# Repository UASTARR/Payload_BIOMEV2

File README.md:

# Payload_BIOMEV2

## TO-DO
- UART
  - ZE27-O3
- Power Distribution
- Connecting SPI and Power

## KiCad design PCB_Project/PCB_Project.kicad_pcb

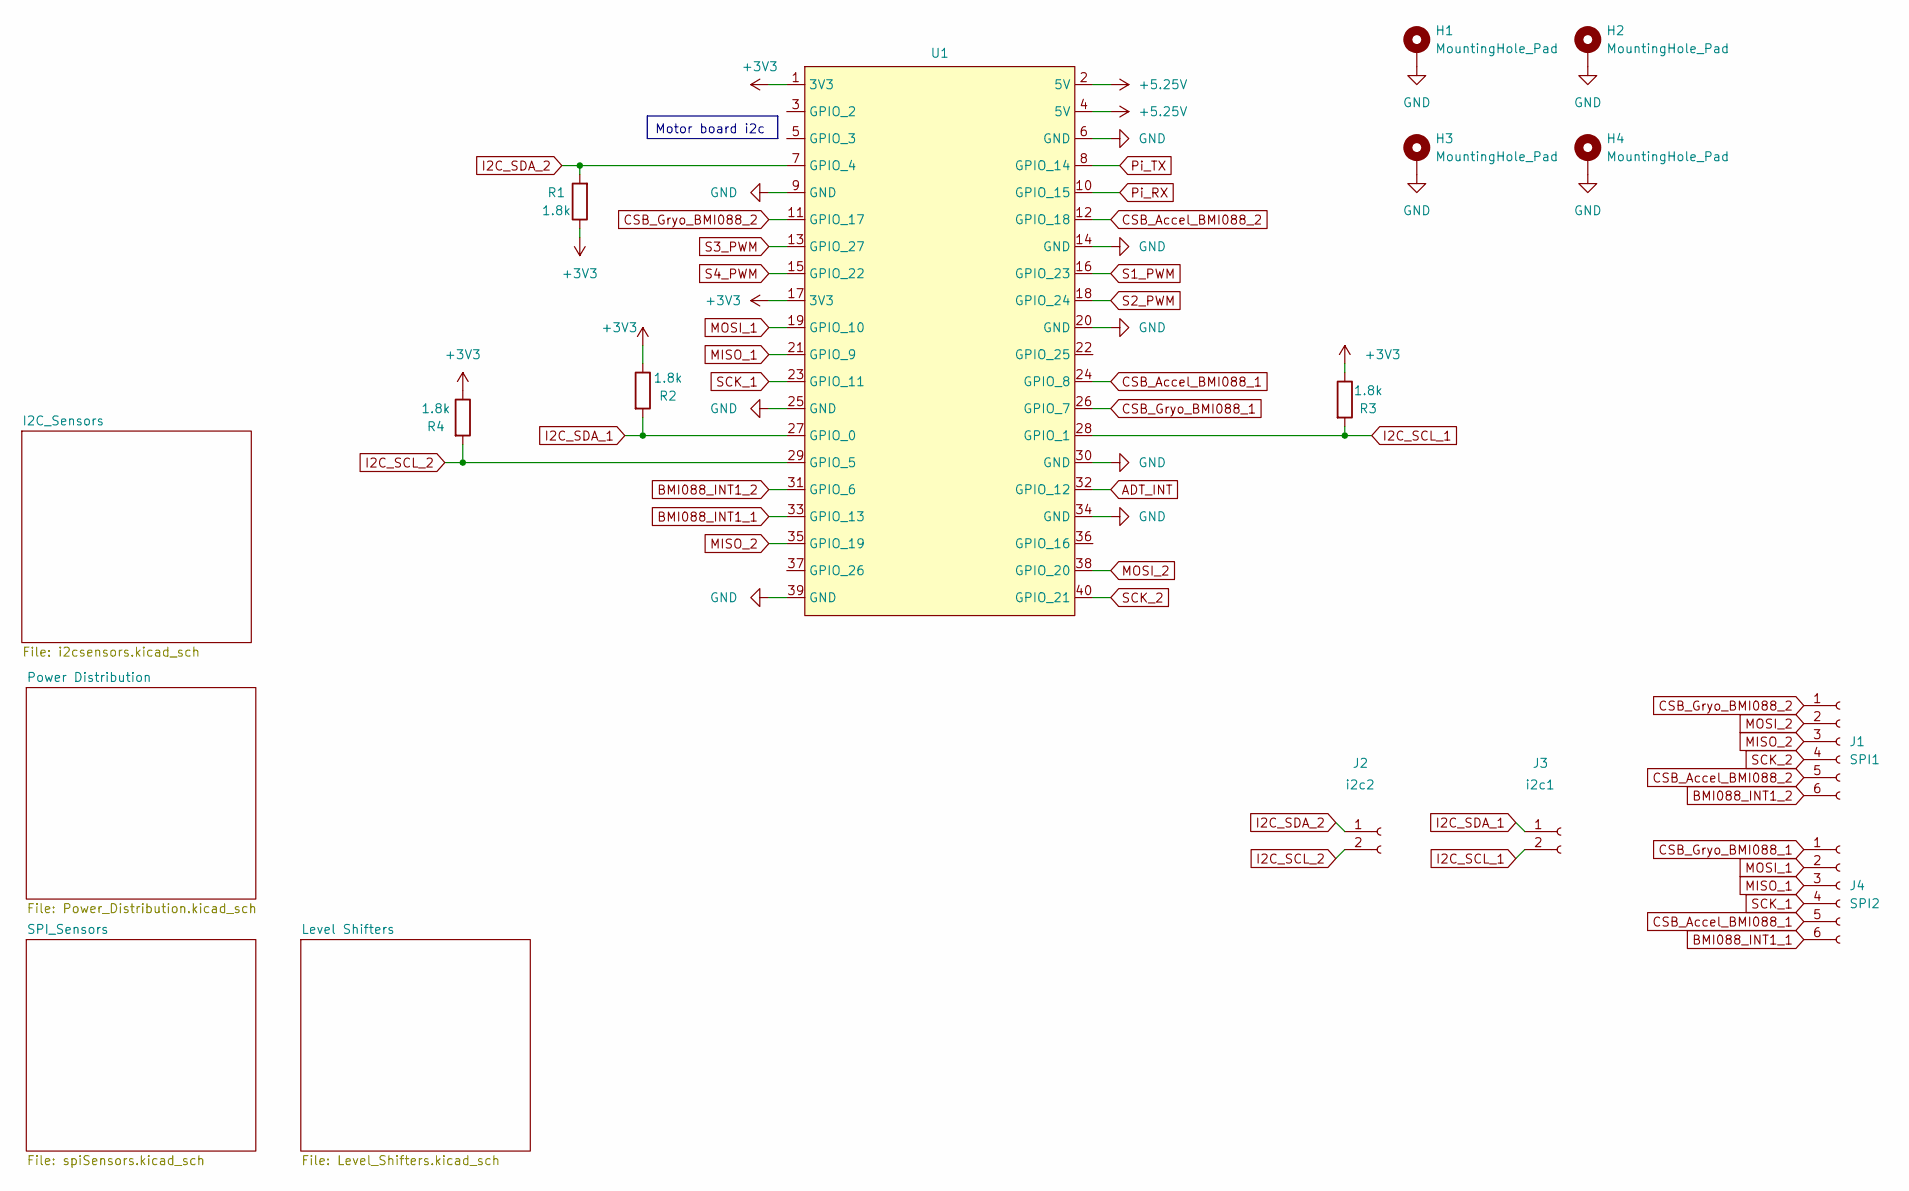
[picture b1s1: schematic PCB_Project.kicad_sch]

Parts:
H1, H2, H3, H4: MountingHole_Pad; MountingHole_2.5mm_Pad
J1: SPI1; PinHeader_1x06_P2.54mm_Vertical
J2: i2c2; JST_PH_B2B-PH-K_1x02_P2.00mm_Vertical
J3: i2c1; JST_PH_B2B-PH-K_1x02_P2.00mm_Vertical
J4: SPI2; PinHeader_1x06_P2.54mm_Vertical
R1, R2, R3, R4: 1.8k; R_0805_2012Metric
U1: PinSocket_2x20_P2.54mm_Vertical

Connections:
+3V3: R1.1, R2.1, R3.1, R4.1, U1.1 (3V3), U1.17 (3V3); also elsewhere on the board
+5.25V: U1.2 (5V), U1.4 (5V); also elsewhere on the board
ADT_INT: U1.32 (GPIO_12); also elsewhere on the board
BMI088_INT1_1: J4.6, U1.33 (GPIO_13); also elsewhere on the board
BMI088_INT1_2: J1.6, U1.31 (GPIO_6); also elsewhere on the board
CSB_Accel_BMI088_1: J4.5, U1.24 (GPIO_8); also elsewhere on the board
CSB_Accel_BMI088_2: J1.5, U1.12 (GPIO_18); also elsewhere on the board
CSB_Gryo_BMI088_1: J4.1, U1.26 (GPIO_7); also elsewhere on the board
CSB_Gryo_BMI088_2: J1.1, U1.11 (GPIO_17); also elsewhere on the board
GND: H1.1, H2.1, H3.1, H4.1, U1.6 (GND), U1.9 (GND), U1.14 (GND), U1.20 (GND), U1.25 (GND), U1.30 (GND), U1.34 (GND), U1.39 (GND); also elsewhere on the board
I2C_SCL_1: J3.2, R3.2, U1.28 (GPIO_1); also elsewhere on the board
I2C_SCL_2: J2.2, R4.2, U1.29 (GPIO_5); also elsewhere on the board
I2C_SDA_1: J3.1, R2.2, U1.27 (GPIO_0); also elsewhere on the board
I2C_SDA_2: J2.1, R1.2, U1.7 (GPIO_4); also elsewhere on the board
MISO_1: J4.3, U1.21 (GPIO_9); also elsewhere on the board
MISO_2: J1.3, U1.35 (GPIO_19); also elsewhere on the board
MOSI_1: J4.2, U1.19 (GPIO_10); also elsewhere on the board
MOSI_2: J1.2, U1.38 (GPIO_20); also elsewhere on the board
Pi_RX: U1.10 (GPIO_15); also elsewhere on the board
Pi_TX: U1.8 (GPIO_14); also elsewhere on the board
S1_PWM: U1.16 (GPIO_23); also elsewhere on the board
S2_PWM: U1.18 (GPIO_24); also elsewhere on the board
S3_PWM: U1.13 (GPIO_27); also elsewhere on the board
S4_PWM: U1.15 (GPIO_22); also elsewhere on the board
SCK_1: J4.4, U1.23 (GPIO_11); also elsewhere on the board
SCK_2: J1.4, U1.40 (GPIO_21); also elsewhere on the board

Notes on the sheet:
Motor board i2c

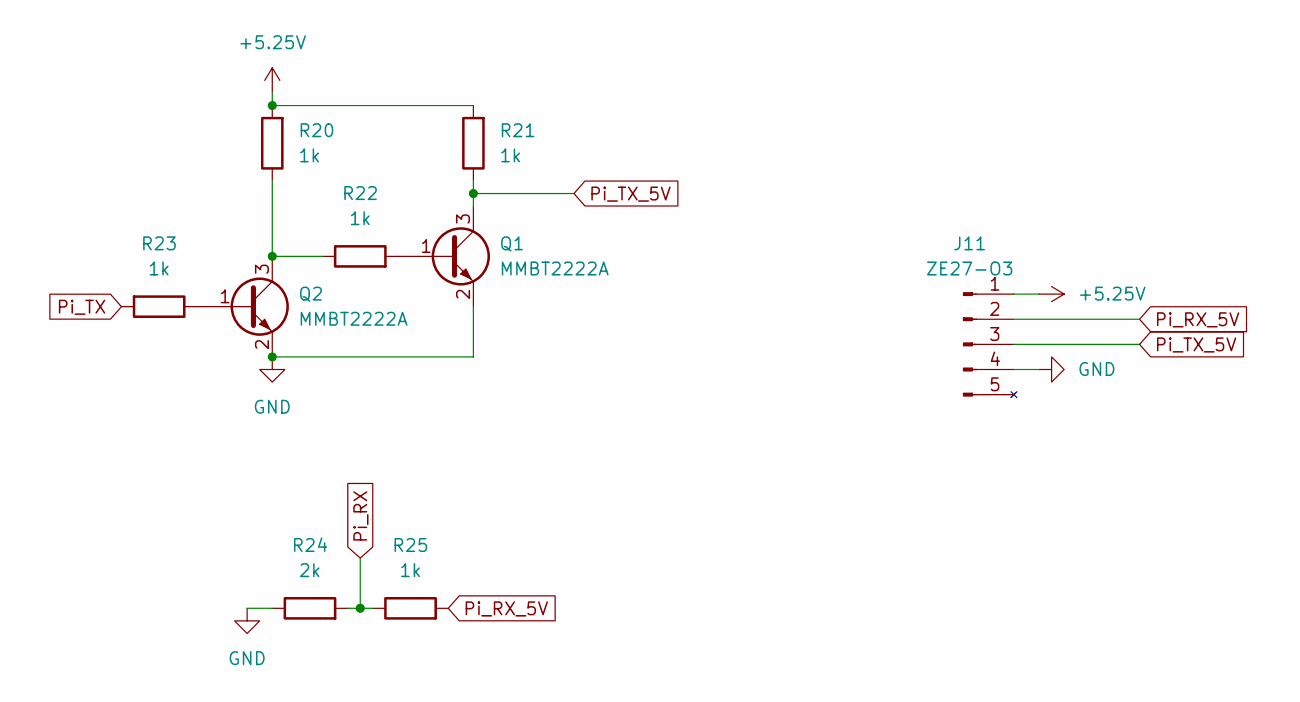
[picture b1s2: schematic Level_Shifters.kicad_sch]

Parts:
J11: ZE27-O3; PinHeader_1x05_P2.00mm_Vertical
Q1, Q2: MMBT2222A; SOT-23
R20, R21, R22, R23, R25: 1k; R_0402_1005Metric
R24: 2k; R_0402_1005Metric

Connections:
+5.25V: J11.1 (Vin), R20.2, R21.2; also elsewhere on the board
GND: J11.4 (GND), Q1.2 (E), Q2.2 (E), R24.1; also elsewhere on the board
unnamed: Q1.1 (B), R22.2
unnamed: Q2.1 (B), R23.1
unnamed: Q2.3 (C), R20.1, R22.1
Pi_RX: R24.2, R25.1; also elsewhere on the board
Pi_RX_5V: J11.2 (UART_TXD_(Out)), R25.2
Pi_TX: R23.2; also elsewhere on the board
Pi_TX_5V: J11.3 (UART_RX_(In)), Q1.3 (C), R21.1

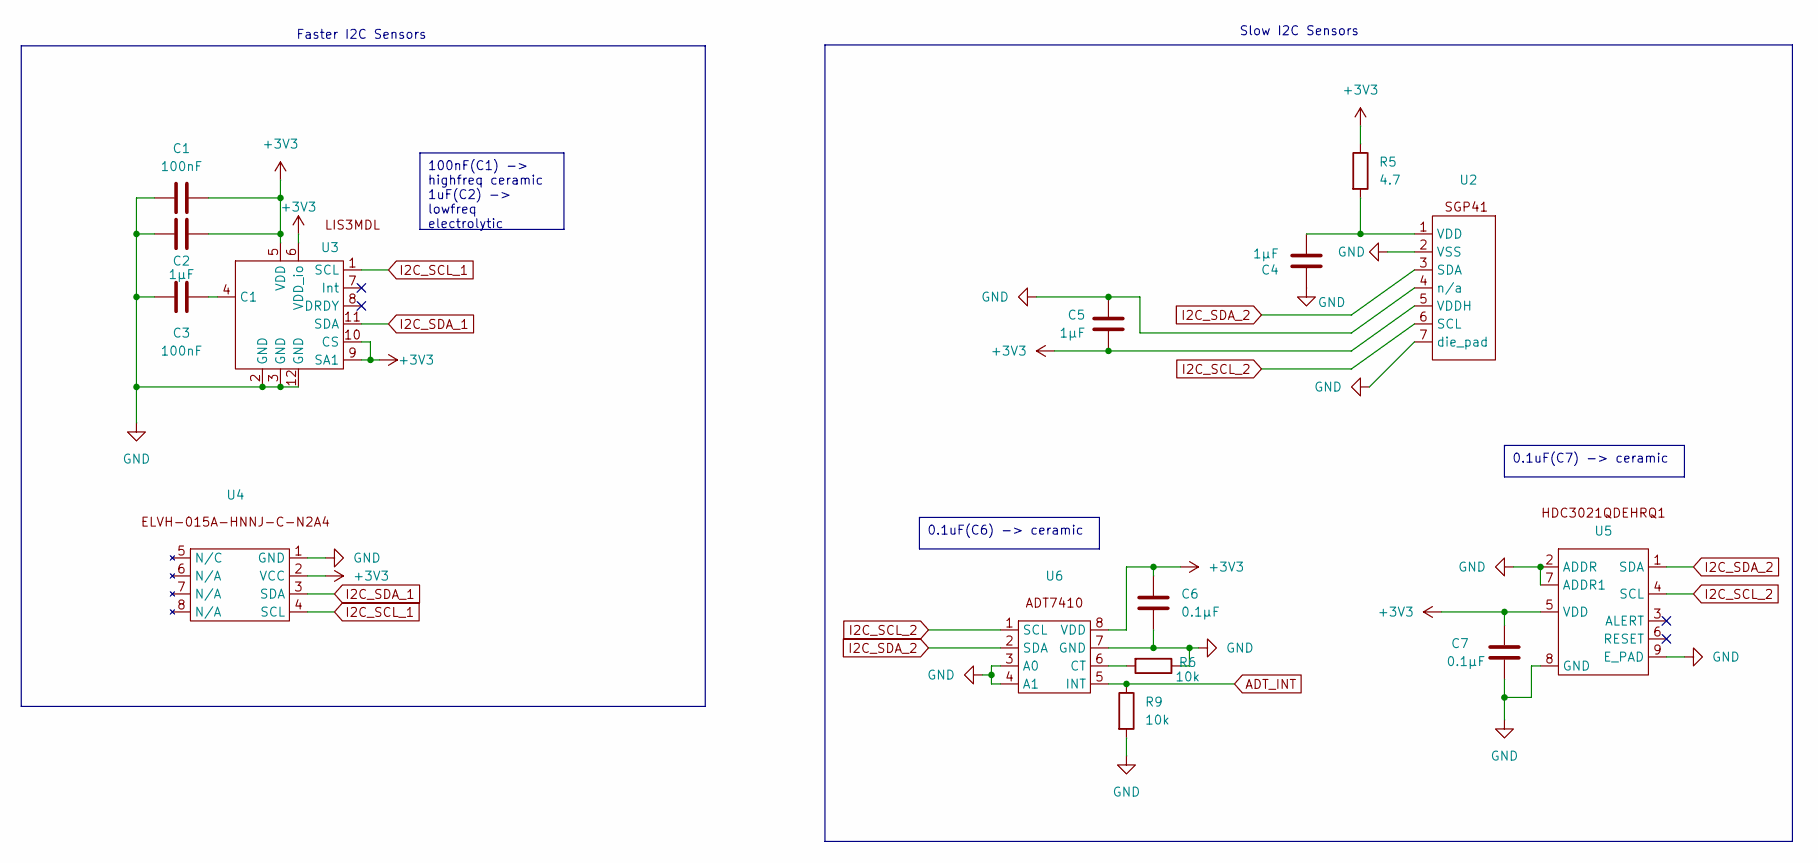
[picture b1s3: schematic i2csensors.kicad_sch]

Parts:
C1, C3: 100nF; C_0402_1005Metric
C2, C4, C5: 1µF; C_0402_1005Metric
C6, C7: 0.1µF; C_0402_1005Metric
R5: 4.7; R_0603_1608Metric
R6, R9: 10k; R_0402_1005Metric
U2: XDCR_SGP41-D-R4
U3: XDCR_LIS3MDL
U4: HNNJ
U5: WSON8_DEH_TEX
U6: SOIC-8

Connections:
+3V3: C1.1, C2.1, C5.2, C6.1, C7.1, R5.1, U2.5 (VDDH), U3.5 (VDD), U3.6 (VDD_io), U3.9 (SA1), U3.10 (CS), U4.2 (VCC), U5.5 (VDD), U6.8 (VDD); also elsewhere on the board
ADT_INT: R9.1, U6.5 (INT); also elsewhere on the board
GND: C1.2, C2.2, C3.2, C4.2, C5.1, C6.2, C7.2, R6.1, R9.2, U2.2 (VSS), U2.4 (n/a), U2.7 (die_pad), U3.2 (GND), U3.3 (GND), U3.12 (GND), U4.1 (GND), U5.2 (ADDR), U5.7 (ADDR1), U5.8 (GND), U5.9 (E_PAD), U6.3 (A0), U6.4 (A1), U6.7 (GND); also elsewhere on the board
I2C_SCL_1: U3.1 (SCL), U4.4 (SCL); also elsewhere on the board
I2C_SCL_2: U2.6 (SCL), U5.4 (SCL), U6.1 (SCL); also elsewhere on the board
I2C_SDA_1: U3.11 (SDA), U4.3 (SDA); also elsewhere on the board
I2C_SDA_2: U2.3 (SDA), U5.1 (SDA), U6.2 (SDA); also elsewhere on the board
unnamed: C4.1, R5.2, U2.1 (VDD)
unnamed: C3.1, U3.4 (C1)
unnamed: R6.2, U6.6 (CT)

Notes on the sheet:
0.1uF(C7) -> ceramic
0.1uF(C6) -> ceramic
100nF(C1) -> highfreq ceramic 1uF(C2) -> lowfreq electrolytic
Slow I2C Sensors
Faster I2C Sensors

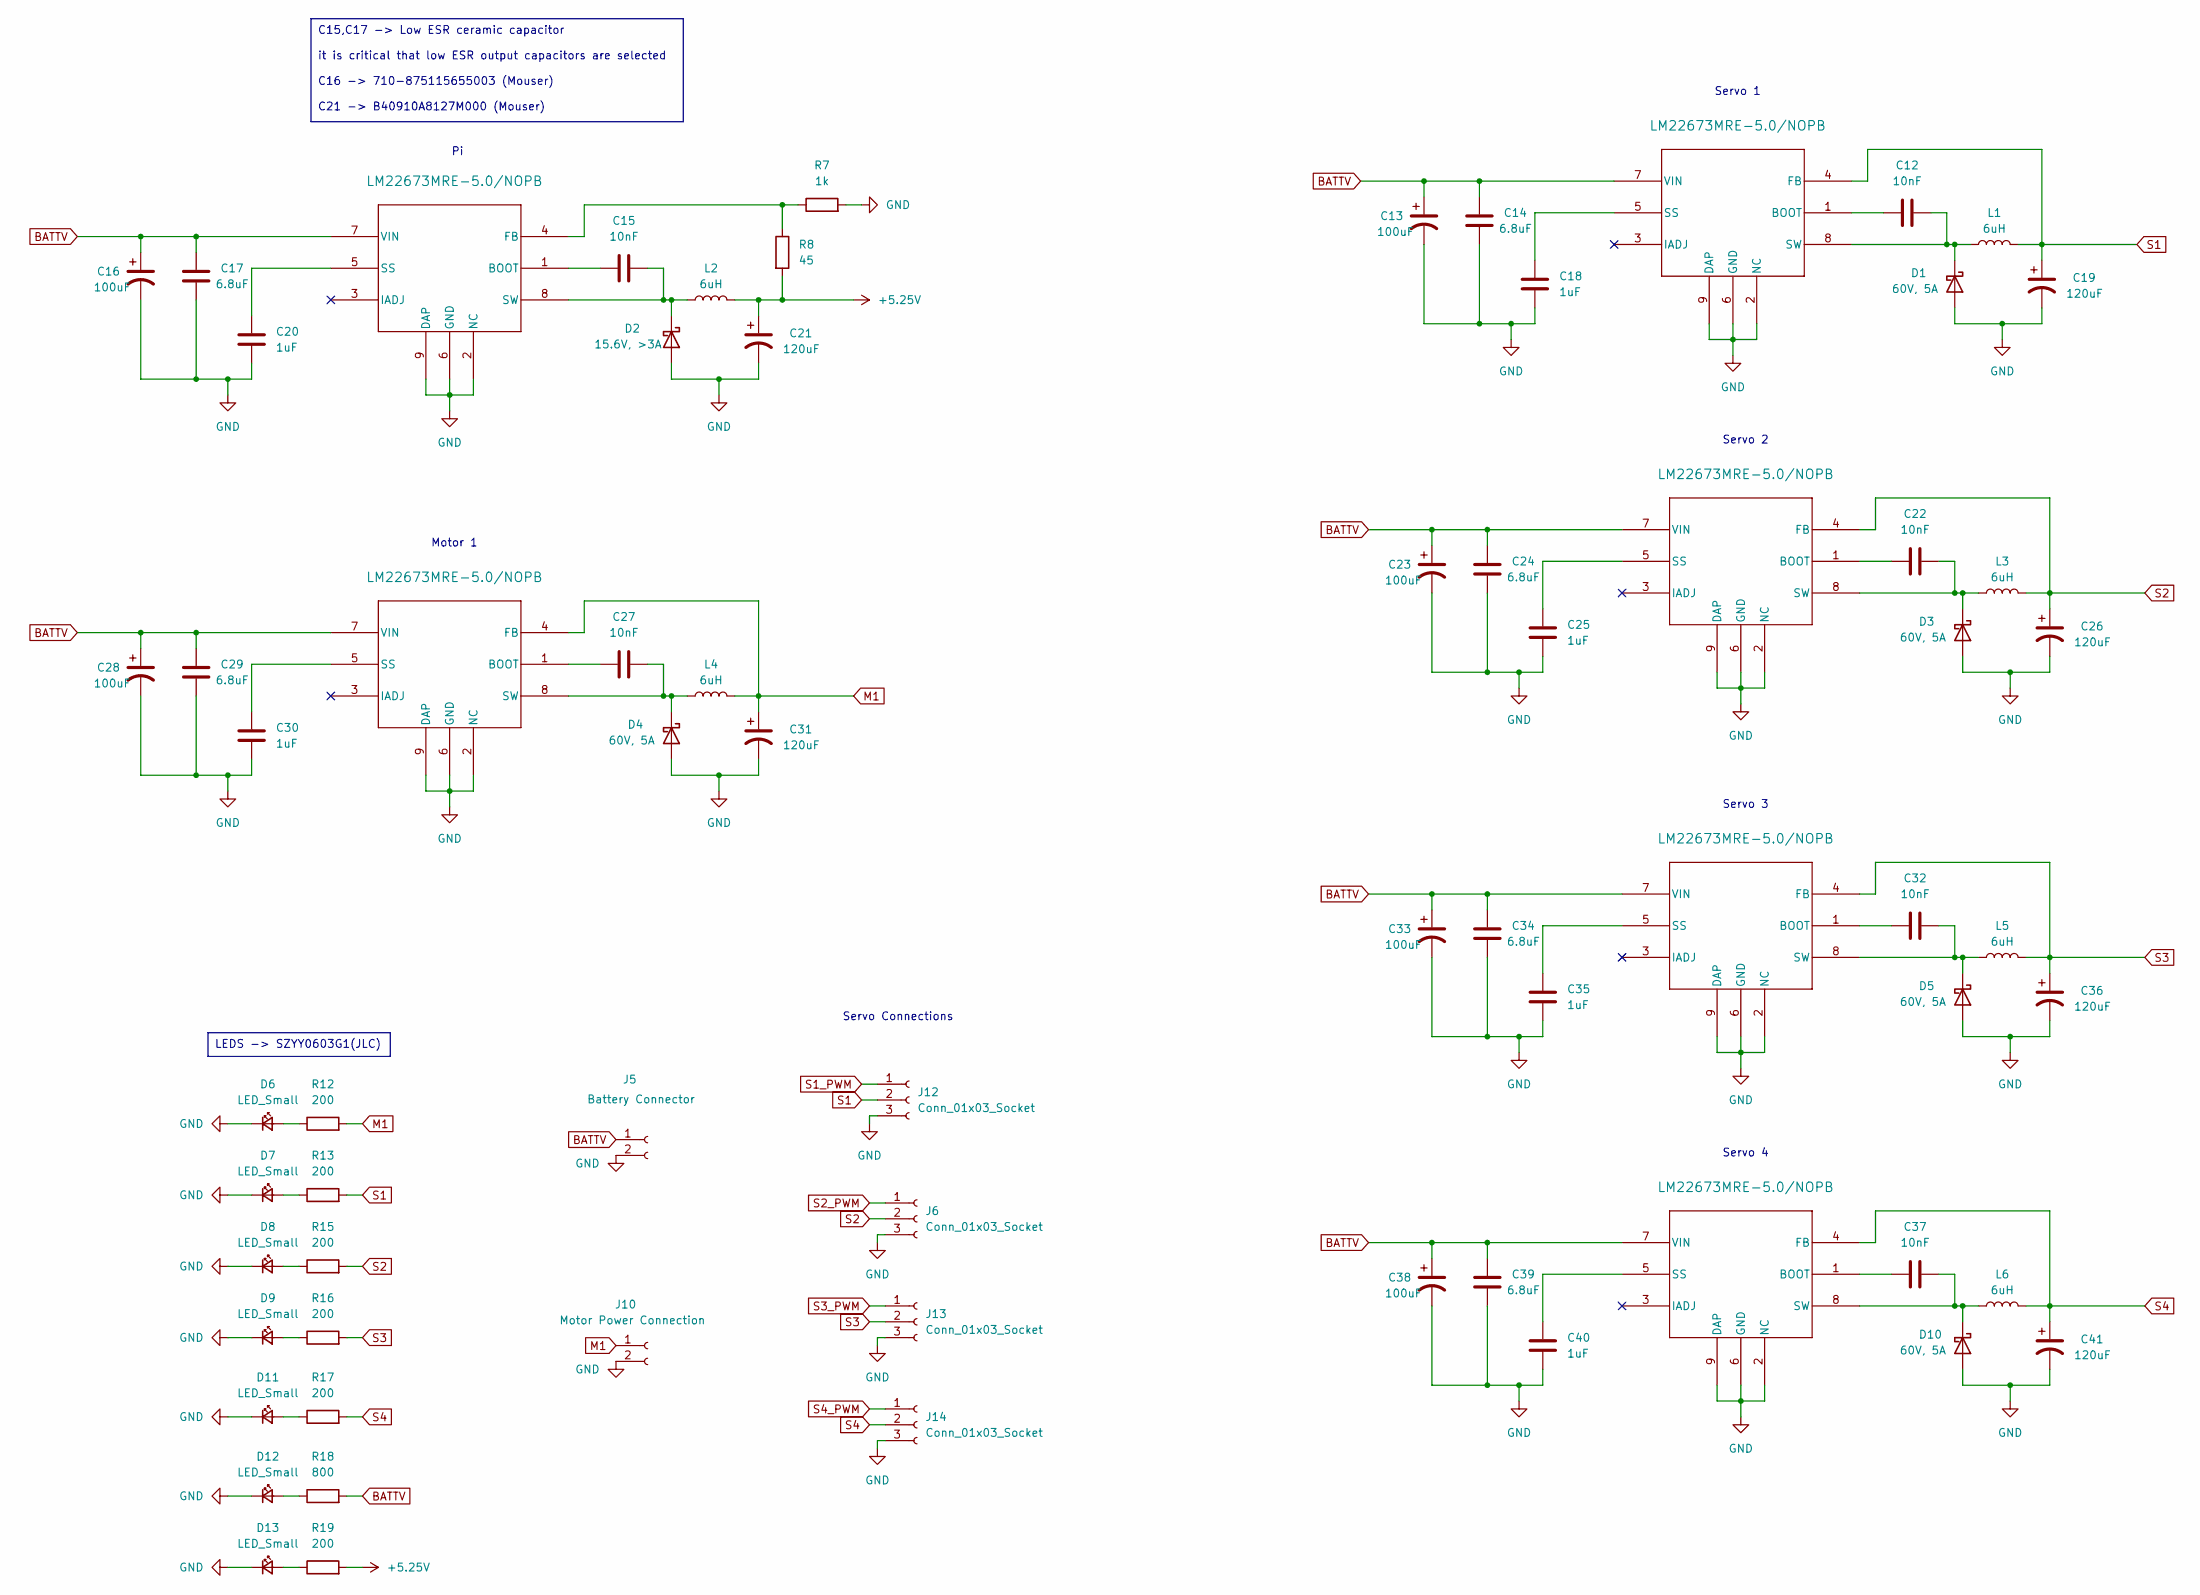
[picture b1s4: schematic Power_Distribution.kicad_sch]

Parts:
111, 1111, 11111, 11112, 11113, 11114: LM22673MRE-5.0/NOPB; MRA08B
C12, C15, C22, C27, C32, C37: 10nF; C_0603_1608Metric
C13, C16, C23, C28, C33, C38: 100uF; CP_WCAP-PSHP
C14, C17, C24, C29, C34, C39: 6.8uF; C_1206_3216Metric
C18, C20, C25, C30, C35, C40: 1uF; C_0603_1608Metric
C19, C21, C26, C31, C36, C41: 120uF; CP_Elec_10x12.5
D1, D3, D4, D5, D10: 60V, 5A; D_PowerDI-5
D2: 15.6V, >3A; D_PowerDI-5
D6, D7, D8, D9, D11, D12, D13: LED_Small; D_0603_1608Metric
J5: Battery Connector; JST_PH_B2B-PH-K_1x02_P2.00mm_Vertical
J6, J12, J13, J14: Conn_01x03_Socket; JST_PH_B3B-PH-K_1x03_P2.00mm_Vertical
J10: Motor Power Connection; JST_PH_B2B-PH-K_1x02_P2.00mm_Vertical
L1, L2, L3, L4, L5, L6: 6uH; L_6.7x6.7mm
R7: 1k; R_0603_1608Metric
R8: 45; R_0603_1608Metric
R12, R13, R15, R16, R17, R19: 200; R_0402_1005Metric
R18: 800; R_0402_1005Metric

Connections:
+5.25V: C21.1, L2.2, R8.2, R19.2; also elsewhere on the board
BATTV: 111.7 (VIN), 1111.7 (VIN), 11111.7 (VIN), 11112.7 (VIN), 11113.7 (VIN), 11114.7 (VIN), C13.1, C14.1, C16.1, C17.1, C23.1, C24.1, C28.1, C29.1, C33.1, C34.1, C38.1, C39.1, J5.1, R18.2
GND: 111.2 (NC), 111.6 (GND), 111.9 (DAP), 1111.2 (NC), 1111.6 (GND), 1111.9 (DAP), 11111.2 (NC), 11111.6 (GND), 11111.9 (DAP), 11112.2 (NC), 11112.6 (GND), 11112.9 (DAP), 11113.2 (NC), 11113.6 (GND), 11113.9 (DAP), 11114.2 (NC), 11114.6 (GND), 11114.9 (DAP), C13.2, C14.2, C16.2, C17.2, C18.2, C19.2, C20.2, C21.2, C23.2, C24.2, C25.2, C26.2, C28.2, C29.2, C30.2, C31.2, C33.2, C34.2, C35.2, C36.2, C38.2, C39.2, C40.2, C41.2, D1.2 (A), D2.2 (A), D3.2 (A), D4.2 (A), D5.2 (A), D6.1 (K), D7.1 (K), D8.1 (K), D9.1 (K), D10.2 (A), D11.1 (K), D12.1 (K), D13.1 (K), J5.2, J6.3, J10.2, J12.3, J13.3, J14.3, R7.2; also elsewhere on the board
M1: 11112.4 (FB), C31.1, J10.1, L4.2, R12.2
unnamed: 111.1 (BOOT), C15.1
unnamed: 111.4 (FB), R7.1, R8.1
unnamed: 111.5 (SS), C20.1
unnamed: 111.8 (SW), C15.2, D2.1 (K), L2.1
unnamed: 1111.1 (BOOT), C12.1
unnamed: 1111.5 (SS), C18.1
unnamed: 1111.8 (SW), C12.2, D1.1 (K), L1.1
unnamed: 11111.1 (BOOT), C22.1
unnamed: 11111.5 (SS), C25.1
unnamed: 11111.8 (SW), C22.2, D3.1 (K), L3.1
unnamed: 11112.1 (BOOT), C27.1
unnamed: 11112.5 (SS), C30.1
unnamed: 11112.8 (SW), C27.2, D4.1 (K), L4.1
unnamed: 11113.1 (BOOT), C32.1
unnamed: 11113.5 (SS), C35.1
unnamed: 11113.8 (SW), C32.2, D5.1 (K), L5.1
unnamed: 11114.1 (BOOT), C37.1
unnamed: 11114.5 (SS), C40.1
unnamed: 11114.8 (SW), C37.2, D10.1 (K), L6.1
unnamed: D6.2 (A), R12.1
unnamed: D7.2 (A), R13.1
unnamed: D8.2 (A), R15.1
unnamed: D9.2 (A), R16.1
unnamed: D11.2 (A), R17.1
unnamed: D12.2 (A), R18.1
unnamed: D13.2 (A), R19.1
S1: 1111.4 (FB), C19.1, J12.2, L1.2, R13.2
S1_PWM: J12.1; also elsewhere on the board
S2: 11111.4 (FB), C26.1, J6.2, L3.2, R15.2
S2_PWM: J6.1; also elsewhere on the board
S3: 11113.4 (FB), C36.1, J13.2, L5.2, R16.2
S3_PWM: J13.1; also elsewhere on the board
S4: 11114.4 (FB), C41.1, J14.2, L6.2, R17.2
S4_PWM: J14.1; also elsewhere on the board

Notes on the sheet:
LEDS -> SZYY0603G1(JLC)
C15,C17 -> Low ESR ceramic capacitor it is critical that low ESR output capacitors are selected C16 -> 710-875115655003 (Mouser) C21 -> B40910A8127M000 (Mouser)
Servo Connections
Servo 4
Motor 1
Servo 1
Servo 3
Servo 2

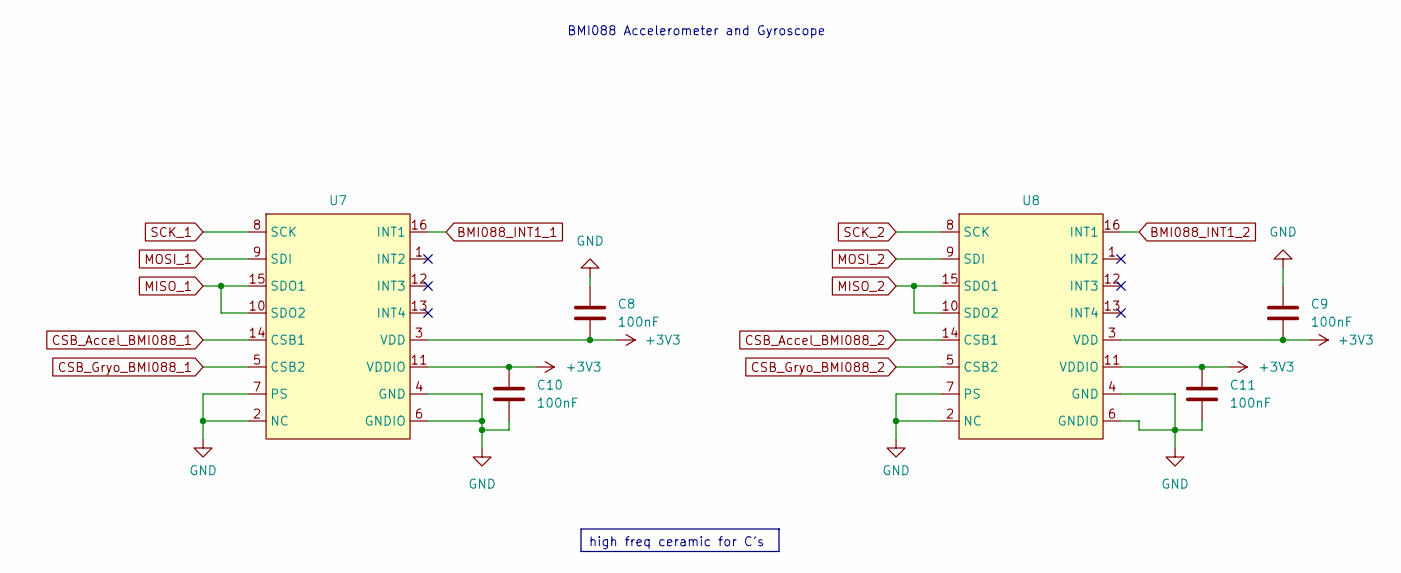
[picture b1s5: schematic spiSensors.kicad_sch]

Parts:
C8, C9, C10, C11: 100nF; C_0402_1005Metric
U7, U8: PQFN50P450X300X100-16N

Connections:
+3V3: C8.1, C9.1, C10.1, C11.1, U7.3 (VDD), U7.11 (VDDIO), U8.3 (VDD), U8.11 (VDDIO); also elsewhere on the board
BMI088_INT1_1: U7.16 (INT1); also elsewhere on the board
BMI088_INT1_2: U8.16 (INT1); also elsewhere on the board
CSB_Accel_BMI088_1: U7.14 (CSB1); also elsewhere on the board
CSB_Accel_BMI088_2: U8.14 (CSB1); also elsewhere on the board
CSB_Gryo_BMI088_1: U7.5 (CSB2); also elsewhere on the board
CSB_Gryo_BMI088_2: U8.5 (CSB2); also elsewhere on the board
GND: C8.2, C9.2, C10.2, C11.2, U7.2 (NC), U7.4 (GND), U7.6 (GNDIO), U7.7 (PS), U8.2 (NC), U8.4 (GND), U8.6 (GNDIO), U8.7 (PS); also elsewhere on the board
MISO_1: U7.10 (SDO2), U7.15 (SDO1); also elsewhere on the board
MISO_2: U8.10 (SDO2), U8.15 (SDO1); also elsewhere on the board
MOSI_1: U7.9 (SDI); also elsewhere on the board
MOSI_2: U8.9 (SDI); also elsewhere on the board
SCK_1: U7.8 (SCK); also elsewhere on the board
SCK_2: U8.8 (SCK); also elsewhere on the board

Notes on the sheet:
high freq ceramic for C's
BMI088 Accelerometer and Gyroscope

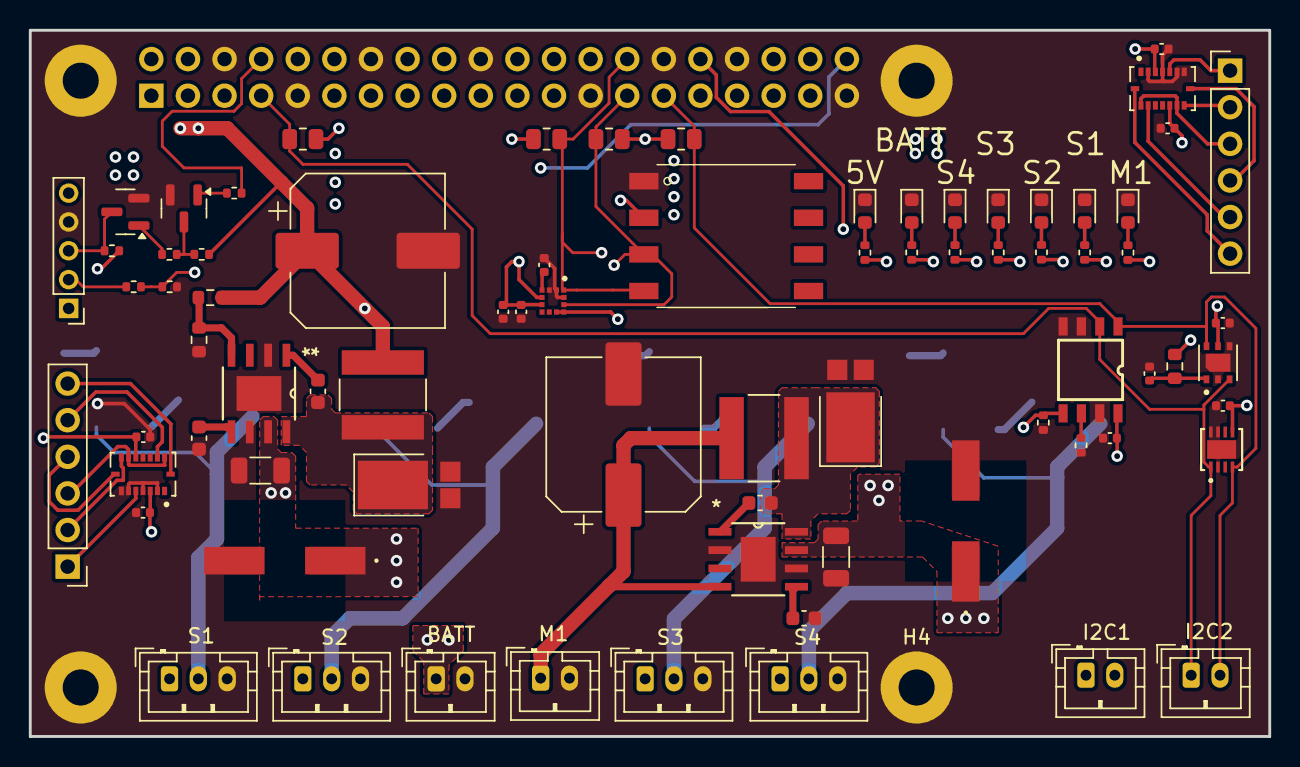
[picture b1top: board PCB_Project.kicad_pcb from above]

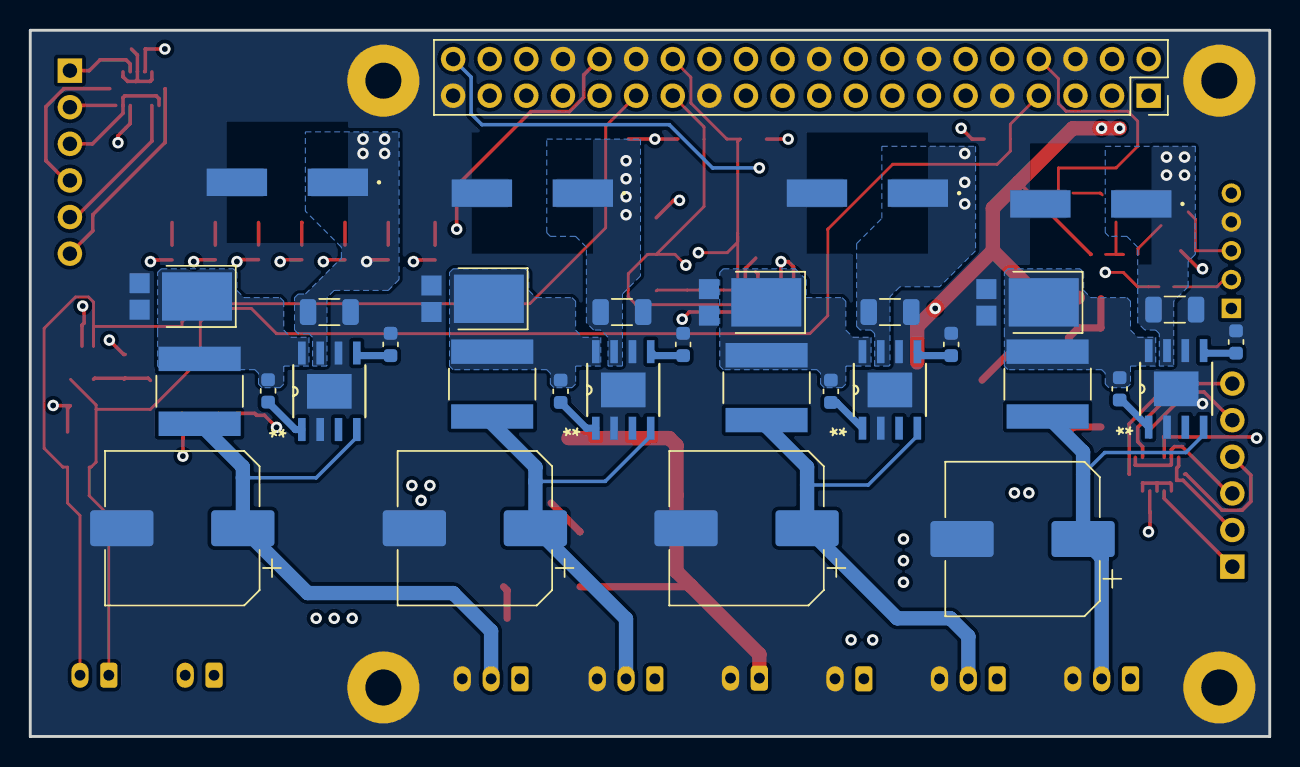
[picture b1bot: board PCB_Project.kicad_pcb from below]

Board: 4 copper layers, 86.0 x 49.0 mm, 113 parts (33 on the bottom side), 66 nets.

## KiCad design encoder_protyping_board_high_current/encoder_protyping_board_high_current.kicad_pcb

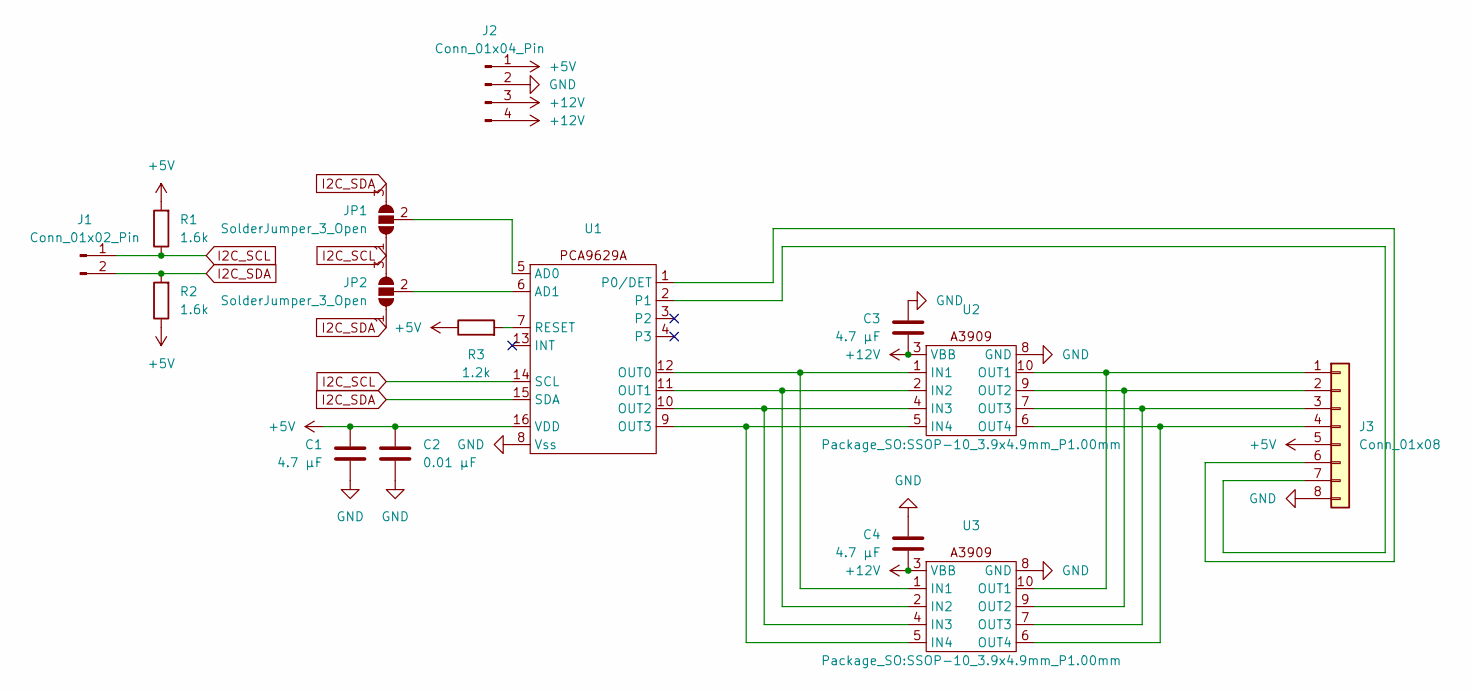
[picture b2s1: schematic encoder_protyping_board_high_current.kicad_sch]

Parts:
C1: 4.7 μF; C_0402_1005Metric
C2: 0.01 μF; C_0402_1005Metric
C3, C4: 4.7 μF; CP_Radial_D5.0mm_P2.00mm
J1: Conn_01x02_Pin; PinHeader_1x02_P2.54mm_Vertical
J2: Conn_01x04_Pin; PinHeader_1x04_P2.54mm_Vertical
J3: Conn_01x08; PinHeader_1x08_P2.54mm_Vertical
JP1, JP2: SolderJumper_3_Open; SolderJumper-3_P1.3mm_Open_RoundedPad1.0x1.5mm_NumberLabels
R1, R2: 1.6k; R_0402_1005Metric
R3: 1.2k; R_0402_1005Metric
U1: TSSOP-16_4.4x5mm_P0.65mm
U2, U3: SSOP-10_3.9x4.9mm_P1.00mm

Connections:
+5V: C1.1, C2.1, J2.1, J3.5, R1.2, R2.1, R3.1, U1.16 (VDD)
+12V: C3.1, C4.1, J2.3, J2.4, U2.3 (VBB), U3.3 (VBB)
GND: C1.2, C2.2, C3.2, C4.2, J2.2, J3.8, U1.8 (Vss), U2.8 (GND), U3.8 (GND)
I2C_SCL: J1.1, JP1.1 (A), JP2.3 (B), R1.1, U1.14 (SCL)
I2C_SDA: J1.2, JP1.3 (B), JP2.1 (A), R2.2, U1.15 (SDA)
unnamed: J3.1, U2.10 (OUT1), U3.10 (OUT1)
unnamed: J3.2, U2.9 (OUT2), U3.9 (OUT2)
unnamed: J3.3, U2.7 (OUT3), U3.7 (OUT3)
unnamed: J3.4, U2.6 (OUT4), U3.6 (OUT4)
unnamed: J3.6, U1.1 (P0/DET)
unnamed: J3.7, U1.2 (P1)
unnamed: JP1.2 (C), U1.5 (AD0)
unnamed: JP2.2 (C), U1.6 (AD1)
unnamed: U1.12 (OUT0), U2.1 (IN1), U3.1 (IN1)
unnamed: U1.11 (OUT1), U2.2 (IN2), U3.2 (IN2)
unnamed: U1.10 (OUT2), U2.4 (IN3), U3.4 (IN3)
unnamed: U1.9 (OUT3), U2.5 (IN4), U3.5 (IN4)
unnamed: R3.2, U1.7 (RESET)

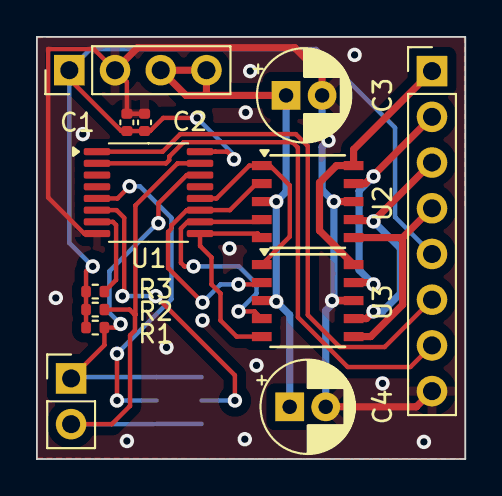
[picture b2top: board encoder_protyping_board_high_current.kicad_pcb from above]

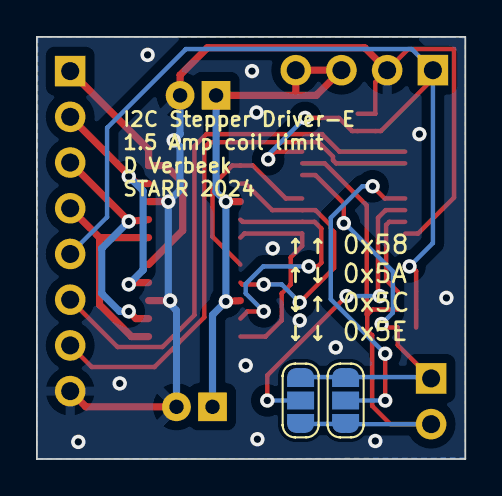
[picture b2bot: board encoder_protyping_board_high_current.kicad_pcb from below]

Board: 2 copper layers, 23.8 x 23.5 mm, 15 parts (2 on the bottom side), 18 nets.

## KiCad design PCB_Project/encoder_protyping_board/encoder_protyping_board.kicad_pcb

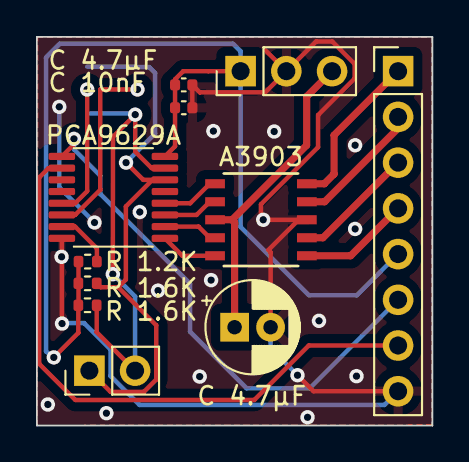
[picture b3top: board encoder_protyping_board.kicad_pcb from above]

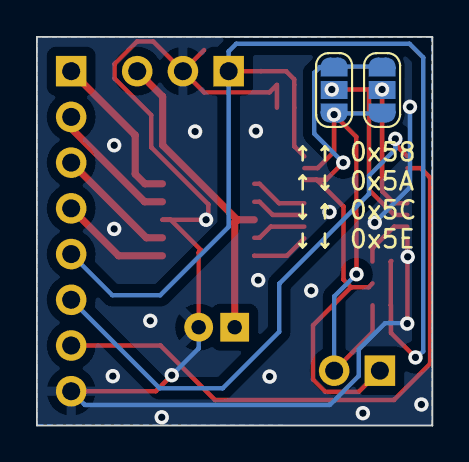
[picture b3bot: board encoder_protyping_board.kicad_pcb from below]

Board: 2 copper layers, 22.0 x 21.6 mm, 13 parts (2 on the bottom side), 18 nets.

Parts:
A3903: SSOP-10_3.9x4.9mm_P1.00mm
C 4.7µF: 4.7 μF; CP_Radial_D5.0mm_P2.00mm
C 4.7µF#2: 4.7 μF; C_0402_1005Metric
C 10nF: 0.01 μF; C_0402_1005Metric
J1: Conn_02x04_Counter_Clockwise; PinHeader_1x08_P2.54mm_Vertical
J2: Conn_01x02_Pin; PinHeader_1x02_P2.54mm_Vertical
J3: Conn_01x03_Pin; PinHeader_1x03_P2.54mm_Vertical
JP1, JP2: SolderJumper_3_Open; SolderJumper-3_P1.3mm_Open_RoundedPad1.0x1.5mm_NumberLabels
PCA9629A: TSSOP-16_4.4x5mm_P0.65mm
R 1.2K: 1.2k; R_0402_1005Metric
R 1.6K, R 1.6K#2: 1.6k; R_0402_1005Metric

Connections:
+5V: C 4.7µF#2.1, C 10nF.1, J1.5, J3.1, PCA9629A.16 (VDD), R 1.2K.1, R 1.6K.2, R 1.6K#2.1
+12V: A3903.3 (VBB), C 4.7µF.1, J3.3
GND: A3903.8 (GND), C 4.7µF.2, C 4.7µF#2.2, C 10nF.2, J1.8, J3.2, PCA9629A.8 (Vss)
I2C_SCL: J2.1, JP1.3 (B), JP2.1 (A), PCA9629A.14 (SCL), R 1.6K.1
I2C_SDA: J2.2, JP1.1 (A), JP2.3 (B), PCA9629A.15 (SDA), R 1.6K#2.2
unnamed: A3903.10 (OUT1), J1.1
unnamed: A3903.9 (OUT2), J1.2
unnamed: A3903.7 (OUT3), J1.3
unnamed: A3903.6 (OUT4), J1.4
unnamed: J1.6, PCA9629A.1 (P0/DET)
unnamed: J1.7, PCA9629A.2 (P1)
unnamed: JP1.2 (C), PCA9629A.6 (AD1)
unnamed: JP2.2 (C), PCA9629A.5 (AD0)
unnamed: A3903.1 (IN1), PCA9629A.12 (OUT0)
unnamed: A3903.2 (IN2), PCA9629A.11 (OUT1)
unnamed: A3903.4 (IN3), PCA9629A.10 (OUT2)
unnamed: A3903.5 (IN4), PCA9629A.9 (OUT3)
unnamed: PCA9629A.7 (RESET), R 1.2K.2

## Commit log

2024-02-16 added kicad init project
2024-02-16 added global labels
2024-02-23 added barebones SPI sensors
2024-02-23 added raspberry pi connector
2024-02-23 cleanup
2024-02-23 added power board
2024-02-23 done for the day work off this now
2024-02-25 First 2 i2c sensors
2024-02-28 LIS3MDL and ELVH-015A-HNNJ-C-N2A4
    bad version of the HDC3021QDEHRQ1 has been removed for now
2024-02-28 I2C done
2024-02-28 changed some symbols still going to clean up a bit
2024-02-28 added decumpiling caps
2024-02-28 clean up thx david!
2024-03-05 ADDR1 on the 3021 is not NC
    it should be going to ground
2024-03-07 ADC mostly added
2024-03-19 motor driver started
    address is 5C
2024-03-19 I2C pullups added
2024-03-20 begone ADC you are not needed
2024-03-20 added the header
2024-03-22 encoder schematic
2024-03-22 the filter cap does not go between the voltage rail and the input pin
2024-03-22 I have probably done so many things wrong
2024-03-23 fixed a trice width and did a bit of rerouting
    0.4mm heading to the motor is all good but does not matter if the 12V power to the chip is not also 0.4mm wide
2024-03-25 more vias on the ground plane and some rerouting
2024-03-25 a better connected ground plane is a happy ground plane
2024-03-25 manual routing is fun
    it is basically a puzzle
2024-03-25 added addresse jumpers
2024-03-25 slightly sorter ground path to U1
2024-03-25 added jumper setting on rear silkscreen
2024-03-25 Labeled part values
2024-03-28 fix my gnd mistake
2024-03-31 lock removed and updated to kicad 8
2024-03-31 ignore how ugly it looks I need to fix it
2024-04-02 working on root sch
2024-04-02 work baby
2024-04-02 2 footprints left then can design
2024-04-02 pcb work
2024-04-02 bunch of things
    added to the rear silkscreen
    moved I2C header to edge of board
    rerouted lines so no signals ran around the edge of the board
    beefed up ground to A3903
    made sure ground was around all edges of the board
    cleaned up the 5v runs
2024-04-04 more cleaning up and adding footprints
2024-04-04 schematic for high current driver
2024-04-04 high current version done
2024-04-04 auto clean up on the board
2024-04-05 pin headers not pin sockets
2024-05-06 need to fix the one damn footprint
2024-05-07 pcb init complete
2024-05-07 added gerber files
2024-05-07 second gerber files
2024-05-07 re commit
2024-05-07 everything is now hooked up
2024-05-07 Fixed resistor value for SGP41
2024-05-07 Swapped Pi_RX and Pi_TX
2024-05-07 Swapped I2C_SDA_1 and I2C_SCL_1
2024-05-07 Rerouted and Cleaned up Board
2024-05-07 added level shifters
2024-05-07 footprints
2024-05-07 Removed lck
2024-05-08 level shifters added to PCB
2024-05-09 soldering it to the board
2024-05-09 Updated .gitignore
2024-05-11 fixes
2024-05-11 finaly did that change to make it so this board could run with just a single chip
2024-05-11 that would have been bad
    changed the outputs to the chips but not the inputs
2024-05-14 added pos files
2024-05-17 clean up and better gerbers so jlc doesnt yell at me
2024-05-17 patch antenna is done
2024-05-17 just a quick cut and paste to move them out
2024-05-17 clean up
2024-05-22 don't worry about this Christiaan
    just starting work on a controll program to run on a pi pico to let us controll the board using a CLI interface
2024-05-22 Create LICENSE
2024-05-23 about half way done
    have to do some bit shifting to get things set write and then write it out still
2024-05-23 this should work
2024-05-24 gain to control of when i2c stop happens
    it executes the current state of the registers on an i2c stop event so lets only send one when we want to
2024-05-25 figured for some things I want to jsut be able to write and send stop at the same time
    also removed the main call which makes it nicer to work with using just teraterm and not VS code
2024-05-25 being able to read would also be nice
    so much untested code at this point
2024-05-26 the read option will only work if I let the input validation hand it back
2024-05-26 qol and refactoring
2024-05-26 register cheat sheet
2024-05-27 fixed some broken stuff and added the first complex function
    all of this is still untested and next up will be doing some real motor control code
2024-05-30 working on final board
2024-06-05 power distribution done
2024-06-06 fixed via's
2024-06-13 added fabs and fixed i2c loop
2024-06-14 removed power board since im simplifing it now
2024-06-26 power baby
2024-06-26 working on pcb
2024-07-03 Swapped JST's and fixed FB connections
2024-07-16 finally
2024-07-16 Cleaned up wiring, Fixed missing BATTV connection
